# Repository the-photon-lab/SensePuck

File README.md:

# SensePuck V0.3 / ESP32-C6 Sensor Board

  ### ⚠️ **This project is under active development. Expect changes.**

**SensePuck is a portable, open-hardware data logger designed for long-term, battery-powered environmental monitoring.** It integrates a powerful ESP32-C6 SoC with a suite of precision sensors, flexible power management, and local data storage, making it a robust platform for applications ranging from remote weather stations to indoor air quality analysis and IoT research.

---

## Key Specifications

| Category | Component / Specification |
| :--- | :--- |
| **MCU** | Espressif ESP32-C6-MINI-1-N4 |
| **Connectivity** | Wi-Fi 6 (802.11ax), Bluetooth 5.3 LE, Zigbee, Thread (802.15.4) |
| **Sensors** | **BME688:** Gas (VOC), Pressure, Humidity, Temperature<br>**SHT40:** High-Accuracy Humidity & Temperature<br>**LTR-390UV:** Ambient Light & UV Index (UVA/UVB) |
| **Power Input** | USB Type-C (Charging & Programming)<br>JST-PH 2-pin connector for 3.7V Single-Cell (1S) LiPo/Li-Ion Battery |
| **Storage** | MicroSD Card Slot with Card Detect |
| **User Interface** | WS2812B-2020 Addressable RGB LED<br>Tactile Push Button (User Input) |

---

## Hardware Details

The core design objective of the SensePuck is to achieve maximum operational endurance from a compact LiPo battery. This is accomplished through a multi-faceted approach:
1.  **Component Selection:** Every critical component was chosen for its ultra-low quiescent current and high efficiency.
2.  **Aggressive Power Gating:** All non-essential peripherals are completely disconnected from the power rails during sleep states using MOSFET-based load switches.
3.  **Hardware-Level Failsafes:** A dedicated voltage supervisor provides robust protection against battery over-discharge and brownout conditions, independent of the main MCU's state.

---

## Power Supply and Battery Management

The power section is designed for efficiency, reliability, and safety in long-term battery-powered applications.

*   **Power Source:** The board is designed to be powered by a standard 3.7V single-cell LiPo battery. A physical **slide switch (S1)** serves as the master On/Off control by controlling the `ENABLE` pin of the TPS62821DLCR buck converter. For development and charging, it uses a **USB-C connector (J1)**. The USB input is protected by a **resettable fuse (F1)** and **ESD protection diodes (U3, D1)** to guard against overcurrent and electrical discharge events.

*   **Battery Charging:** The **MCP73831T (U4)** is a dedicated LiPo/Li-Ion charge management controller IC that provides reliable single-cell charging. The charge current is set to ~200mA via resistor **R14**, a conservative value suitable for a wide range of small LiPo batteries. A P-Channel MOSFET **(Q3)** provides reverse-polarity protection for the battery. The MCU can monitor the charging state (`Charging`/`Done`) via the `CHG_STAT` pin.

*   **Voltage Regulation:**
    *   **Component:** The system's 3.3V rail is generated by the **Texas Instruments TPS62821DLCR (U2)**. This synchronous buck converter was chosen specifically for its **60 nA quiescent current (Iq)**. An LDO was avoided due to the significant efficiency loss when converting from a 4.2V-3.3V LiPo source. The TPS62821's high efficiency (>90% across a wide load range) and ultra-low Iq are paramount for maximizing battery life during the long deep-sleep periods that dominate the device's operational time.
    *   **Implementation:** The feedback network (**R10+R11, R12**) sets the stable 3.3V output. The converter is enabled or disabled via its `EN` pin, allowing for a complete system shutdown.

*   **Hardware Failsafe:** A common failure point in battery-powered devices is unstable operation when the battery voltage drops. As the battery voltage falls below 3.3V, a standard buck converter enters "dropout mode," where it can no longer regulate, and the output voltage sags along with the battery. This can cause the ESP32 to enter a "brownout" state, leading to unpredictable resets, corrupted data on the SD card, or a boot-loop that quickly kills the battery.

    To prevent this, SensePuck incorporates a **TLV803EC30DBZR (U1) voltage supervisor**.
    *   It **independently** monitors the battery voltage, completely separate from the MCU, and consumes only ~0.4µA.
    *   If the voltage drops below its fixed threshold of ~3V, the supervisor **immediately and automatically disables the buck converter** by pulling its `EN` (Enable) pin low.
    *   This forces a **clean, hard shutdown**, preventing the entire system from operating with an unstable power supply. It also serves as the main protection against over-discharging and permanently damaging the battery, even if the main firmware has crashed.

This hardware-based approach is more reliable than a software-only voltage check, which cannot prevent brownouts caused by sudden current spikes (e.g., Wi-Fi activation) or protect the battery if the software hangs.

---

## Power Gating

To minimize deep-sleep current, high-side switching using low Rds(on) P-Channel MOSFETs (**AO3401A**) is employed to completely disconnect peripherals from their power source. This strategy reduces the sleep current from hundreds of µA (if peripherals were left in standby) to the single-digit µA range, dominated only by the leakage of the core components.

---

## Sensor Power Control

The BME688, SHT40, and LTR-390UV are gated by a single MOSFET **(Q5)**, controlled by `SENSOR_ENABLE`. The firmware brings this pin `LOW` only for the duration of a measurement, powering the entire sensor suite. Once measurements are complete, the pin is driven `HIGH`, turning off the MOSFET and eliminating all quiescent current from the sensors. A pi filter composed of a **ferrite bead (FL1)** and capacitors is placed on this switched rail to provide clean, stable power to the sensitive analog front-ends of the sensors, ensuring measurement accuracy.

---

## SD Card and RGB LED Power Control

This same power-gating principle is applied to the other major peripherals:

*   **SD Card (Q1):** MicroSD cards can have an idle current draw of over 100µA. MOSFET **Q1**, controlled by `SD_ENABLE`, ensures the card is only powered when a file operation is active. The `SD_DETECT` switch in the socket allows the firmware to avoid powering the rail if no card is present.
*   **RGB LED (Q4):** The **WS2812B2020 LED (D3)** also has a small quiescent draw. MOSFET **Q4**, controlled by `LED_ON`, ensures it draws zero current when not in use. A 100-ohm series resistor (**R15**) on the data line serves as a protective measure and helps match impedance, improving signal integrity.

---

## MCU and Measurement Circuits

*   **MCU (U7):** The ESP32-C6-MINI-1 was selected for its blend of modern connectivity (Wi-Fi 6), low-power modes (deep-sleep with LP core), and native USB for simplified programming. Its power input is isolated with its own ferrite bead filter **(FL2)** to reduce noise from the rest of the system.
*   **Power-Gated Battery Measurement:** A simple resistive divider for measuring battery voltage would constantly drain the battery. To solve this, the divider (**R17, R18**) is gated by MOSFET **Q2**. To perform a measurement, the firmware executes a "sample-and-hold" logic:
    1.  Drive `VBAT_MEASURE_ON` pin `LOW`.
    2.  This activates Q2, connecting the divider to the battery rail.
    3.  A brief delay allows the voltage at the ADC pin to stabilize.
    4.  The ADC is triggered to take a sample.
    5.  `VBAT_MEASURE_ON` is immediately driven `HIGH`, deactivating Q2.
    This entire process takes only a few milliseconds, and the divider only draws current during this tiny window, making the energy cost of voltage measurement negligible.

## Component & Pinout Overview

### Key Components

| Reference | Component               | Description                                                                    | I2C Address |
| :-------- | :---------------------- | :----------------------------------------------------------------------------- | :---------- |
| U7        | ESP32-C6-MINI-1-N4      | Main Microcontroller with Wi-Fi 6, BT5, Zigbee, Thread                         | -           |
| U5        | BME688                  | Temperature, Humidity, Pressure & Gas (VOC) Sensor                             | `0x76`      |
| U8        | SHT40-AD1B-R3CT-ND      | High-Precision Temperature & Humidity Sensor                                   | `0x44`      |
| U6        | LTR-390UV-01            | Ambient Light & UV Sensor                                                      | `0x53`      |
| U4        | MCP73831T-2ACI_OT       | Li-Ion/Li-Polymer Battery Charge Management Controller                         | -           |
| U2        | TPS62821DLCR            | High-Efficiency 3.3V Step-Down Converter                                       | -           |
| J2        | 104031-0811             | MicroSD Card Socket                                                            | -           |
| D3        | WS2812B2020             | Addressable RGB LED for status indication                                      | -           |

### ESP32-C6 Pinout

| ESP32-C6 Pin | GPIO | Function | Schematic Net Name | Notes |
| :--- | :--- | :--- | :--- | :--- |
| 12 | IO0 | User Button | `BUTTON` | Connected to tactile switch S2. Can be used to wake from deep-sleep. |
| 13 | IO1 | LED Power Enable | `LED_ON` | `LOW` = On, `HIGH` = Off (Controls P-channel MOSFET Q4) |
| 5 | IO2 | LTR-390UV Interrupt | `LTR_INT` | Active-low interrupt. Can be used to wake from deep-sleep on light events. |
| 6 | IO3 | Charger Status Read | `CHG_STAT` | `LOW` = Charging, `HIGH`/`Z` = Done/No Power |
| 9 | IO4 | Battery Measurement ADC | `VBAT_MEASURE_ADC` | ADC input for the power-gated voltage divider. |
| 10 | IO5 | Battery Measurement Enable | `VBAT_MEASURE_ON` | `LOW` = On, `HIGH` = Off (Controls P-channel MOSFET Q2) |
| 15 | IO6 | I2C Data | `I2C_SDA` | I2C bus for all sensors. |
| 16 | IO7 | I2C Clock | `I2C_SCL` | I2C bus for all sensors. |
| 23 | IO9 | Force Bootloader Mode | `BOOT` | Pulled high. Short to GND during reset to enter ROM bootloader. |
| 19 | IO14 | Sensor Power Enable | `SENSOR_ENABLE` | `LOW` = On, `HIGH` = Off (Controls P-channel MOSFET Q5) |
| 20 | IO15 | SD Card Power Enable | `SD_ENABLE` | `LOW` = On, `HIGH` = Off (Controls P-channel MOSFET Q1) |
| 24 | IO18 | SPI MOSI for SD Card | `SD_MOSI` | SPI Command Line |
| 25 | IO19 | SPI MISO for SD Card | `SD_MISO` | SPI Data Line 0 |
| 26 | IO20 | SPI Clock for SD Card | `SD_SCK` | SPI Clock Line |
| 27 | IO21 | SPI Chip Select for SD Card | `SD_CS` | SPI Data Line 3 / Chip Select |
| 28 | IO22 | SD Card Detect | `SD_DETECT` | `LOW` when card is inserted. |
| 29 | IO23 | LED Data | `LED_DATA` | Data line for WS2812B RGB LED. |

---

## Firmware

**Coming Soon!**

The firmware for the SensePuck is currently under development. It will be built using the ESP-IDF framework for complete control of the MCU's peripherals to ensure ultra-low power operation.

### Board Bring-Up

*   **Entering Bootloader Mode:** To flash the board for the first time, you must put the ESP32-C6 into bootloader mode. Short circuit the **BOOT** pads, connect the USB-C cable, and then release.
*   **Debugging:** The headers J4 (TX) and J5 (RX) expose the ESP32-C6's primary hardware UART. This can be used with an external USB-to-Serial adapter for low-level debugging.

This board is also compatible with . YAML Configuration will be provided soon.

---

## License

This project is open source hardware, licensed under the **CERN Open Hardware Licence Version 2 - Permissive (CERN-OHL-P v2)**.

You are welcome to use, modify, manufacture, and distribute this hardware design, provided you give credit to the original author and include the original copyright and license notice. For the full license details, please see the `LICENSE` file included in this repository.

A `NOTICE` file with licensor and project details is also included, as required by the license.

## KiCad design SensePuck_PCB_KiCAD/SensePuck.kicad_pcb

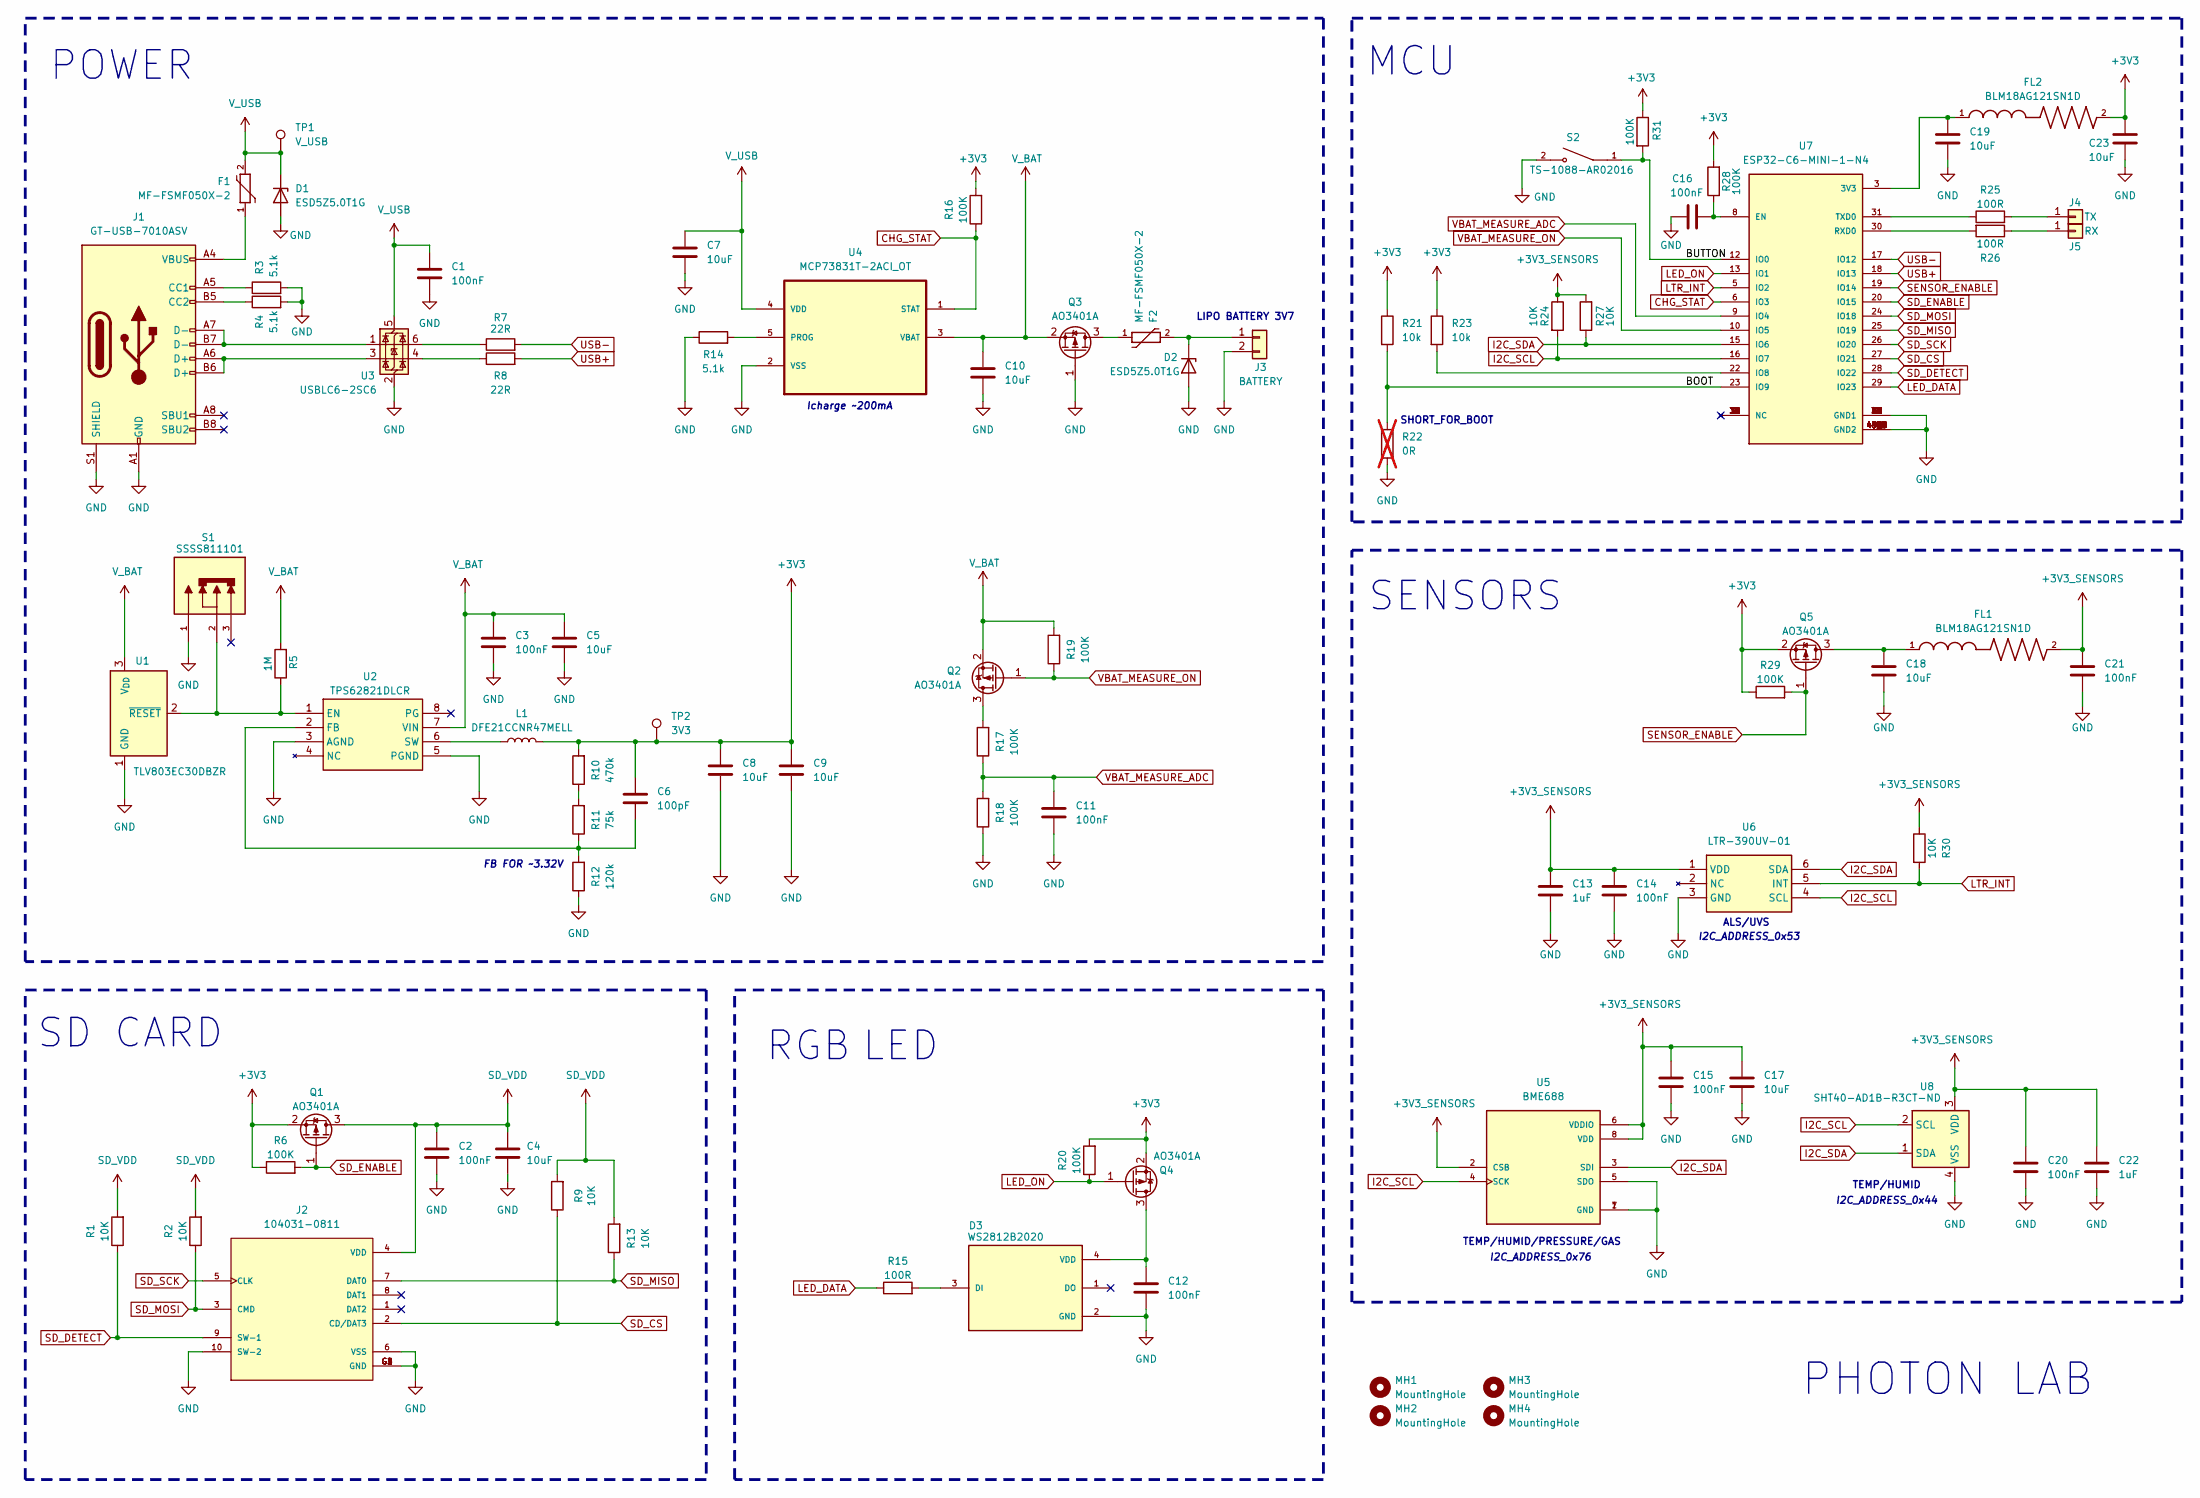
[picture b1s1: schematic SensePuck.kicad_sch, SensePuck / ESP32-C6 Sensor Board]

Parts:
C1, C2, C3, C11, C12, C14, C15, C16, C20, C21: 100nF; C_0603_1608Metric
C4, C5, C7, C8, C9, C10, C17, C18, C19, C23: 10uF; C_0603_1608Metric
C6: 100pF; C_0603_1608Metric
C13, C22: 1uF; C_0603_1608Metric
D1, D2: ESD5Z5.0T1G; D_SOD-523
D3: WS2812B2020; LED_WS2812B2020; PARTREV V1.0
F1, F2: MF-FSMF050X-2; 0603-F1608X100N; MPN MF-FSMF050X-2
FL1, FL2: BLM18AG121SN1D; BEADC1608X95N
J1: GT-USB-7010ASV; USB_C_Receptacle_G-Switch_GT-USB-7010ASV
J2: 104031-0811; MOLEX_104031-0811; PARTREV B2
J3: BATTERY; Hirose_DF13-02P-1.25DSA_1x02_P1.25mm_Vertical
J4: TX; PinHeader_1x01_P1.00mm_Vertical
J5: RX; PinHeader_1x01_P1.00mm_Vertical
L1: DFE21CCNR47MELL; L_0805_2012Metric
MH1, MH2, MH3, MH4: MountingHole; MountingHole_2.2mm_M2
Q1, Q2, Q3, Q4, Q5: AO3401A; SOT-23
R1, R2, R9, R13, R24, R27, R30: 10K; R_0603_1608Metric
R3, R4, R14: 5.1k; R_0603_1608Metric
R5: 1M; R_0603_1608Metric
R6, R16, R17, R18, R19, R20, R28, R29, R31: 100K; R_0603_1608Metric
R7, R8: 22R; R_0603_1608Metric
R10: 470k; R_0603_1608Metric
R11: 75k; R_0603_1608Metric
R12: 120k; R_0603_1608Metric
R15, R25, R26: 100R; R_0603_1608Metric
R21, R23: 10k; R_0603_1608Metric
R22: 0R; R_0603_1608Metric; not fitted
S1: SSSS811101; SW_SSSS811101; PARTREV N/A
S2: TS-1088-AR02016; SW_TS-1088-AR02016; PARTREV N/A
TP1: V_USB; Pin_D1.0mm_L10.0mm
TP2: 3V3; Pin_D1.0mm_L10.0mm
U1: TLV803EC30DBZR; SOT-23-3
U2: TPS62821DLCR; SON50P150X200X100-8N; Mouser Part Number 595-TPS62821DLCR
U3: USBLC6-2SC6; SOT-23-6
U4: MCP73831T-2ACI_OT; SOT95P280X145-5N; MPN MCP73831T-2ACI/OT
U5: BME688; IC_BME688; PARTREV 1.0
U6: LTR-390UV-01; Mouser Part Number 859-LTR390UV01
U7: ESP32-C6-MINI-1-N4; XCVR_ESP32-C6-MINI-1-N4; PARTREV 1.0
U8: SHT40-AD1B-R3CT-ND; Sensirion_DFN-4_1.5x1.5mm_P0.8mm_SHT4x_NoCentralPad

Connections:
+3V3: C6.1, C8.1, C9.1, C23.1, FL2.2, L1.2, Q1.2 (S), Q4.2 (S), Q5.2 (S), R6.1, R10.2, R16.2, R20.2, R21.1, R23.1, R28.2, R29.1, R31.1, TP2.1
+3V3_SENSORS: C13.1, C14.1, C15.1, C17.1, C20.1, C21.1, C22.1, FL1.2, R24.1, R27.2, R30.1, U5.2 (CSB), U5.6 (VDDIO), U5.8 (VDD), U6.1 (VDD), U8.3 (VDD)
/BOOT: R21.2, R22.1, U7.23 (IO9); also elsewhere on the board
/BUTTON: R31.2, S2.1, U7.12 (IO0)
CHG_STAT: R16.1, U4.1 (STAT), U7.6 (IO3)
GND: C1.2, C2.2, C3.2, C4.2, C5.2, C7.2, C8.2, C9.2, C10.2, C11.2, C12.2, C13.2, C14.2, C15.2, C16.1, C17.2, C18.2, C19.2, C20.2, C21.2, C22.2, C23.2, D1.2 (A), D2.2 (A), D3.2 (GND), J1.A1 (GND), J1.A12 (GND), J1.B1 (GND), J1.B12 (GND), J1.S1 (SHIELD), J2.6 (VSS), J2.10 (SW-2), J2.G1 (GND), J2.G2 (GND), J2.G3 (GND), J2.G4 (GND), J3.2, Q3.1 (G), R3.2, R4.2, R12.1, R14.1, R18.1, R22.2, S1.1, S2.2, U1.1 (GND), U2.3 (AGND), U2.5 (PGND), U3.2 (GND), U4.2 (VSS), U5.1 (GND), U5.5 (SDO), U5.7 (GND), U6.3 (GND), U7.1 (GND1), U7.2 (GND1), U7.11 (GND1), U7.14 (GND1), U7.36 (GND1), U7.37 (GND1), U7.38 (GND1), U7.39 (GND1), U7.40 (GND1), U7.41 (GND1), U7.42 (GND1), U7.43 (GND1), U7.44 (GND1), U7.45 (GND1), U7.46 (GND1), U7.47 (GND2), U7.48 (GND2), U7.49_1 (GND2), U7.49_2 (GND2), U7.49_3 (GND2), U7.49_4 (GND2), U7.49_5 (GND2), U7.49_6 (GND2), U7.49_7 (GND2), U7.49_8 (GND2), U7.49_9 (GND2), U7.50 (GND2), U7.51 (GND2), U7.52 (GND2), U7.53 (GND2), U8.4 (VSS); also elsewhere on the board
I2C_SCL: R24.2, U5.4 (SCK), U6.4 (SCL), U7.16 (IO7), U8.2 (SCL)
I2C_SDA: R27.1, U5.3 (SDI), U6.6 (SDA), U7.15 (IO6), U8.1 (SDA)
LED_DATA: R15.1, U7.29 (IO23)
LED_ON: Q4.1 (G), R20.1, U7.13 (IO1)
LTR_INT: R30.2, U6.5 (INT), U7.5 (IO2)
unnamed: D2.1 (K), F2.2, J3.1
unnamed: D3.3 (DI), R15.2
unnamed: C12.1, D3.4 (VDD), Q4.3 (D)
unnamed: F1.1, J1.A4 (VBUS), J1.A9 (VBUS), J1.B4 (VBUS), J1.B9 (VBUS)
unnamed: J1.A5 (CC1), R3.1
unnamed: J1.B5 (CC2), R4.1
unnamed: J1.A6 (D+), J1.B6 (D+), U3.3 (I/O2)
unnamed: J1.A7 (D-), J1.B7 (D-), U3.1 (I/O1)
unnamed: J4.1, R25.2
unnamed: J5.1, R26.1
unnamed: Q2.3 (D), R17.2
unnamed: F2.1, Q3.3 (D)
unnamed: C18.1, FL1.1, Q5.3 (D)
unnamed: R7.1, U3.6 (I/O1)
unnamed: R8.1, U3.4 (I/O2)
unnamed: R10.1, R11.2
unnamed: R5.1, S1.2, U1.2 (~RESET), U2.1 (EN)
unnamed: C6.2, R11.1, R12.2, U2.2 (FB)
unnamed: L1.1, U2.6 (SW)
unnamed: R14.2, U4.5 (PROG)
unnamed: C19.1, FL2.1, U7.3 (3V3)
unnamed: C16.2, R28.1, U7.8 (EN)
unnamed: R23.2, U7.22 (IO8)
unnamed: R26.2, U7.30 (RXD0)
unnamed: R25.1, U7.31 (TXD0)
SD_CS: J2.2 (CD/DAT3), R9.1, U7.27 (IO21)
SD_DETECT: J2.9 (SW-1), R1.1, U7.28 (IO22)
SD_ENABLE: Q1.1 (G), R6.2, U7.20 (IO15)
SD_MISO: J2.7 (DAT0), R13.1, U7.25 (IO19)
SD_MOSI: J2.3 (CMD), R2.1, U7.24 (IO18)
SD_SCK: J2.5 (CLK), U7.26 (IO20)
SD_VDD: C2.1, C4.1, J2.4 (VDD), Q1.3 (D), R1.2, R2.2, R9.2, R13.2
SENSOR_ENABLE: Q5.1 (G), R29.2, U7.19 (IO14)
USB+: R8.2, U7.18 (IO13)
USB-: R7.2, U7.17 (IO12)
VBAT_MEASURE_ADC: C11.1, R17.1, R18.2, U7.9 (IO4)
VBAT_MEASURE_ON: Q2.1 (G), R19.1, U7.10 (IO5)
V_BAT: C3.1, C5.1, C10.1, Q2.2 (S), Q3.2 (S), R5.2, R19.2, U1.3 (V_{DD}), U2.7 (VIN), U4.3 (VBAT)
V_USB: C1.1, C7.1, D1.1 (K), F1.2, TP1.1, U3.5 (VBUS), U4.4 (VDD)

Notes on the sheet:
TEMP/HUMID/PRESSURE/GAS
POWER
FB FOR ~3.32V
I2C_ADDRESS_0x76
I2C_ADDRESS_0x53
SD CARD
SHORT_FOR_BOOT
LED
PHOTON LAB
LIPO BATTERY 3V7
I2C_ADDRESS_0x44
ALS/UVS
MCU
Icharge ~200mA
TEMP/HUMID
SENSORS

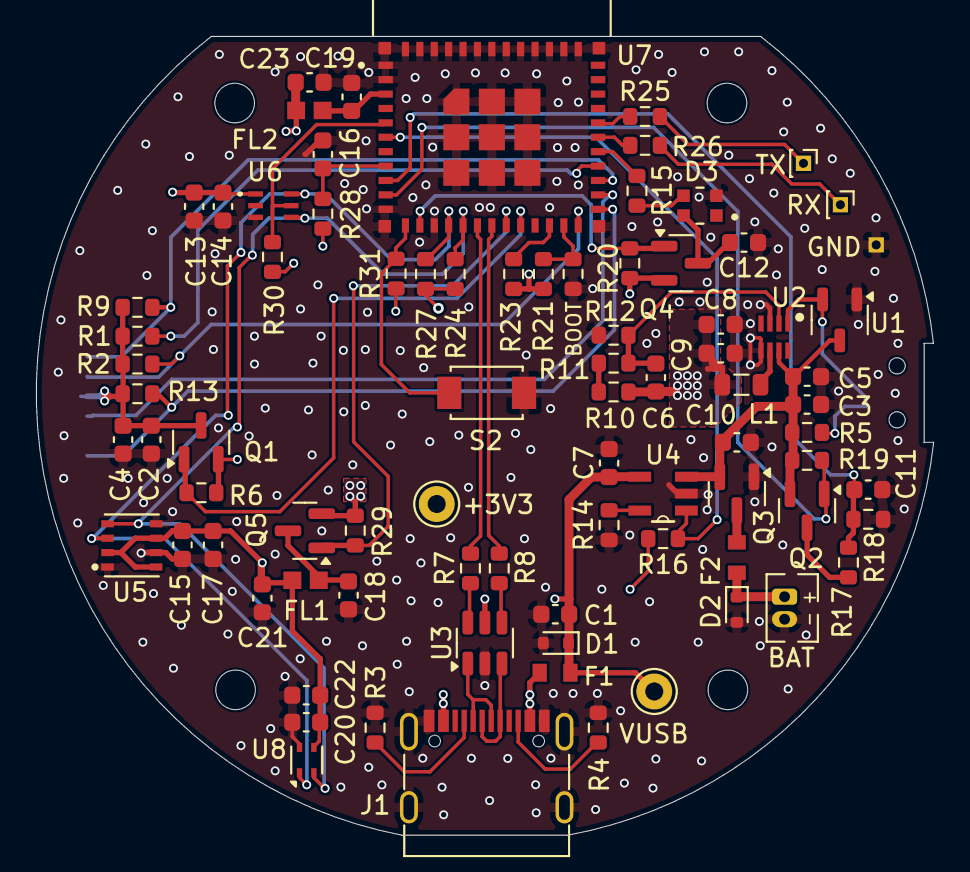
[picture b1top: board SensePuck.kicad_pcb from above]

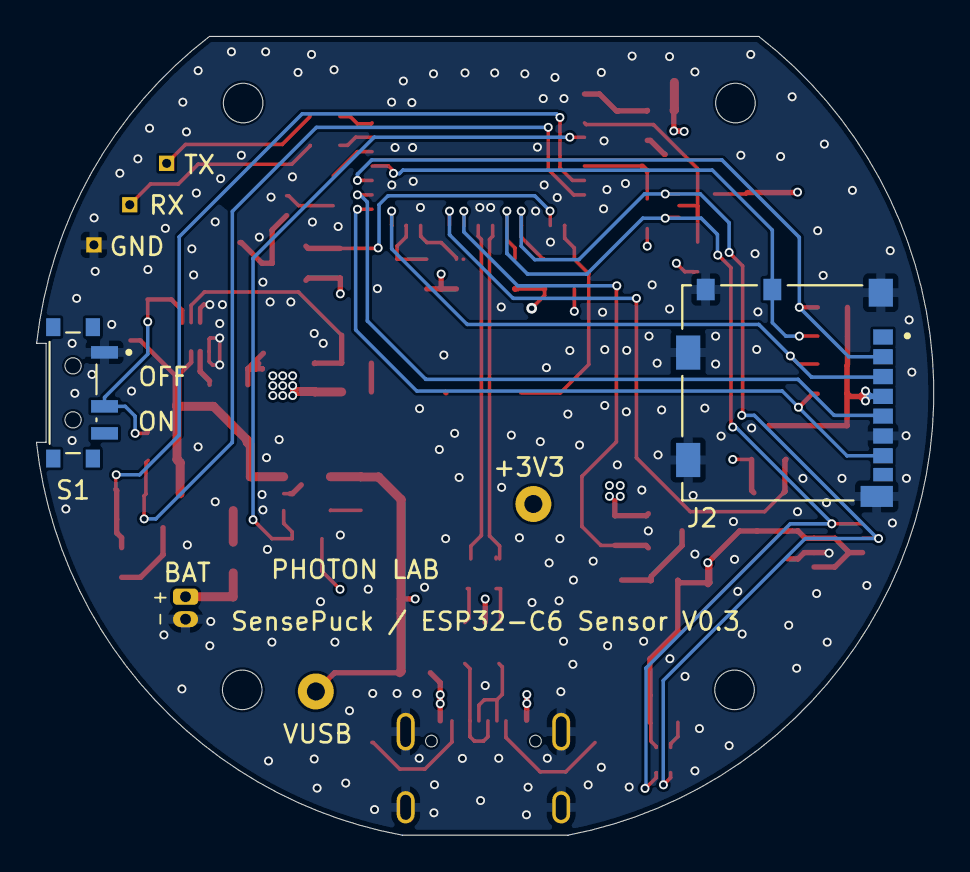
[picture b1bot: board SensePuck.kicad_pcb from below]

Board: 4 copper layers, 49.8 x 44.4 mm, 88 parts (2 on the bottom side), 50 nets.

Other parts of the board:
BOOT: 0R; R_0603_1608Metric

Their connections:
/BOOT: BOOT.1; also elsewhere on the board
GND: BOOT.2; also elsewhere on the board

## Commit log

2025-08-15 Update NOTICE
2025-08-26 Update README.md
    Update README.md
